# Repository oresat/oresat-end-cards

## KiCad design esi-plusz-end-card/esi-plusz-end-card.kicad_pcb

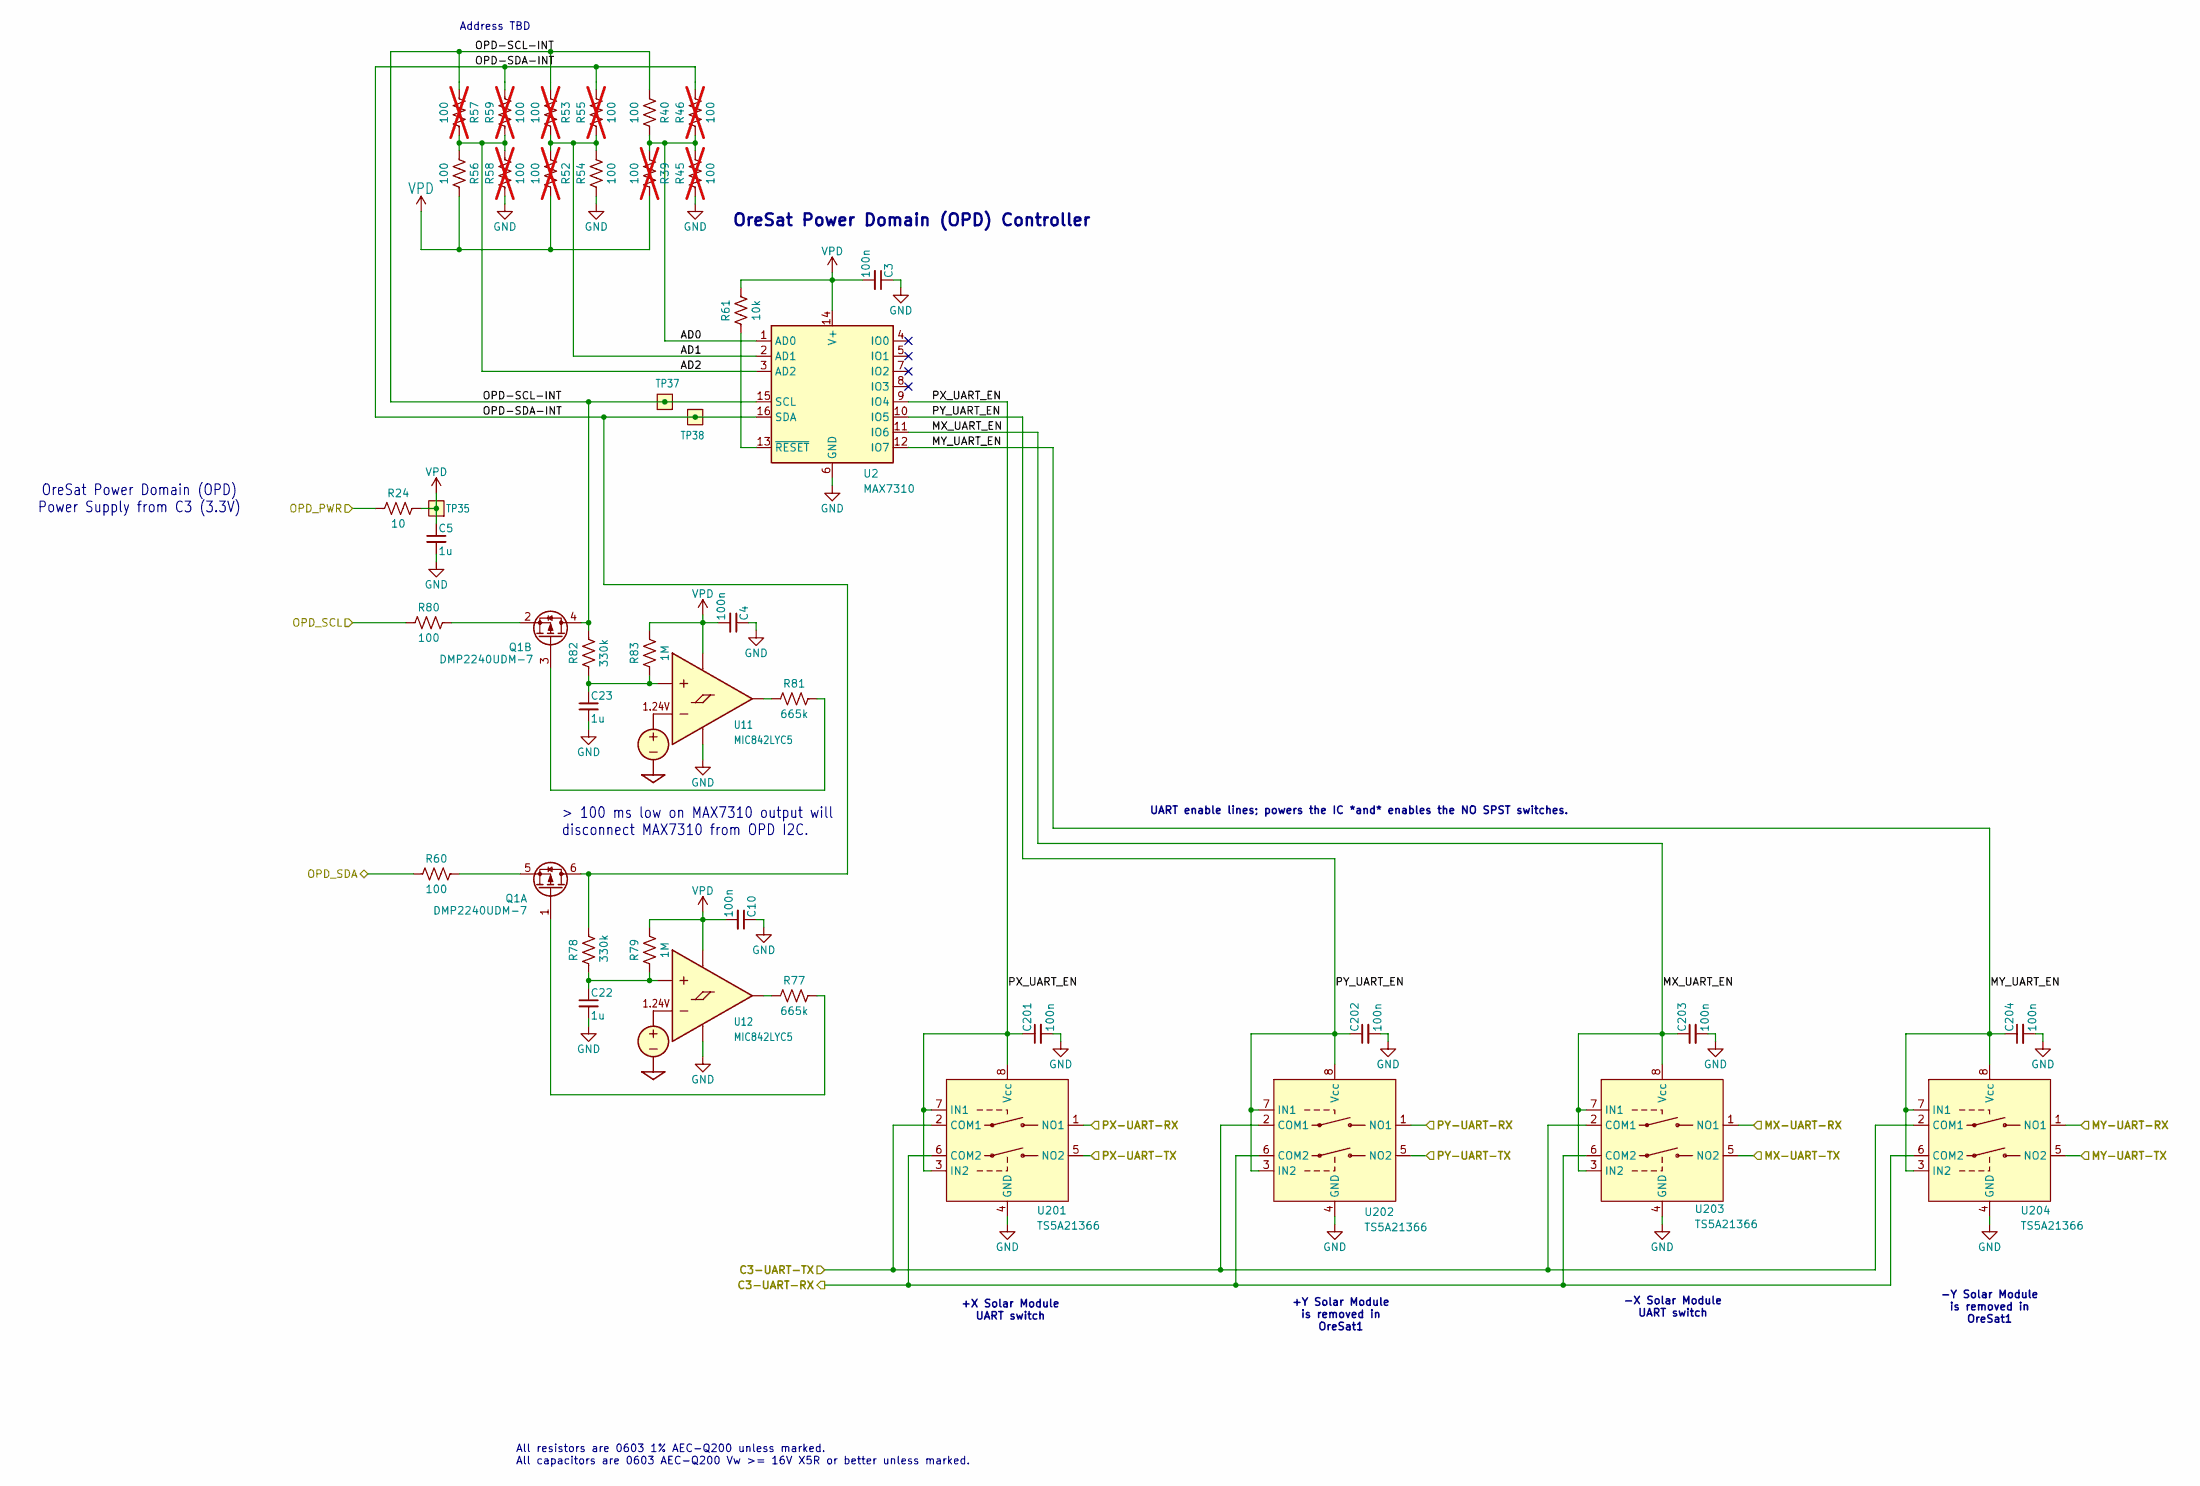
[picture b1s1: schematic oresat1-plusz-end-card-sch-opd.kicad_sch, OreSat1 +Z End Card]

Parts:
C3, C4, C10, C201, C202, C203, C204: 100n; 0603-C-NOSILK; MPN C0603C104K5RACAUTO
C5, C22, C23: 1u; 0603-C-NOSILK; MPN GRT188R71E105KE13D
Q1: DMP2240UDM-7; SOT-23-6; MPN DMP2240UDM-7
R24: 10; 0603-C-NOSILK; MPN RMCF0603FT10R0
R39, R45, R46, R52, R53, R55, R57, R58, R59: 100; 0603-C-NOSILK; MPN RMCF0603FT100R; not fitted
R40, R54, R56, R60, R80: 100; 0603-C-NOSILK; MPN RMCF0603FT100R
R61: 10k; 0603-C-NOSILK; MPN RMCF0603FT10K0
R77, R81: 665k; 0603-C-NOSILK; MPN RMCF0603FT665K
R78, R82: 330k; 0603-C-NOSILK; MPN RMCF0603FT330K
R79, R83: 1M; 0603-C-NOSILK; MPN RMCF0603FT1M00
TP35, TP37, TP38: Test-Point; TestPoint-0.75mm-th
U2: MAX7310; QFN-16-1EP_4x4mm_P0.65mm_EP2.1x2.1mm; MPN MAX7310ATE+
U11, U12: MIC842LYC5; SOT-353_SC-70-5; MPN MIC842LYC5-TR
U201, U202, U203, U204: TS5A21366; VSSOP-8_2.3x2mm_P0.5mm; MPN TS5A21366DCUR

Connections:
/+Z EC OreSat Power Domain (OPD)/AD0: R39.1, R40.2, R45.2, R46.1, U2.1 (AD0)
/+Z EC OreSat Power Domain (OPD)/AD1: R52.1, R53.2, R54.2, R55.1, U2.2 (AD1)
/+Z EC OreSat Power Domain (OPD)/AD2: R56.1, R57.2, R58.2, R59.1, U2.3 (AD2)
/+Z EC OreSat Power Domain (OPD)/MX-UART-RX: U203.1 (NO1); also elsewhere on the board
/+Z EC OreSat Power Domain (OPD)/MX-UART-TX: U203.5 (NO2); also elsewhere on the board
/+Z EC OreSat Power Domain (OPD)/MX_UART_EN: C203.1, U2.11 (IO6), U203.3 (IN2), U203.7 (IN1), U203.8 (Vcc)
/+Z EC OreSat Power Domain (OPD)/MY-UART-RX: U204.1 (NO1); also elsewhere on the board
/+Z EC OreSat Power Domain (OPD)/MY-UART-TX: U204.5 (NO2); also elsewhere on the board
/+Z EC OreSat Power Domain (OPD)/MY_UART_EN: C204.1, U2.12 (IO7), U204.3 (IN2), U204.7 (IN1), U204.8 (Vcc)
/+Z EC OreSat Power Domain (OPD)/OPD-SCL-INT: Q1.4 (D), R40.1, R53.1, R57.1, R82.2, TP37.1 (1_1), U2.15 (SCL)
/+Z EC OreSat Power Domain (OPD)/OPD-SDA-INT: Q1.6 (D), R46.2, R55.2, R59.2, R78.2, TP38.1 (1_1), U2.16 (SDA)
/+Z EC OreSat Power Domain (OPD)/PX-UART-RX: U201.1 (NO1); also elsewhere on the board
/+Z EC OreSat Power Domain (OPD)/PX-UART-TX: U201.5 (NO2); also elsewhere on the board
/+Z EC OreSat Power Domain (OPD)/PX_UART_EN: C201.1, U2.9 (IO4), U201.3 (IN2), U201.7 (IN1), U201.8 (Vcc)
/+Z EC OreSat Power Domain (OPD)/PY-UART-RX: U202.1 (NO1); also elsewhere on the board
/+Z EC OreSat Power Domain (OPD)/PY-UART-TX: U202.5 (NO2); also elsewhere on the board
/+Z EC OreSat Power Domain (OPD)/PY_UART_EN: C202.1, U2.10 (IO5), U202.3 (IN2), U202.7 (IN1), U202.8 (Vcc)
/C3_UART_RX: U201.6 (COM2), U202.6 (COM2), U203.6 (COM2), U204.6 (COM2); also elsewhere on the board
/C3_UART_TX: U201.2 (COM1), U202.2 (COM1), U203.2 (COM1), U204.2 (COM1); also elsewhere on the board
/OPD_PWR: R24.1; also elsewhere on the board
/OPD_SCL: R80.1; also elsewhere on the board
/OPD_SDA: R60.1; also elsewhere on the board
GND: C3.1, C4.1, C5.2, C10.1, C22.2, C23.2, C201.2, C202.2, C203.2, C204.2, R45.1, R54.1, R58.1, U2.6 (GND), U2.17 (GND), U11.2 (GND), U12.2 (GND), U201.4 (GND), U202.4 (GND), U203.4 (GND), U204.4 (GND); also elsewhere on the board
unnamed: Q1.1 (G), R77.2
unnamed: Q1.5 (S), R60.2
unnamed: Q1.3 (G), R81.2
unnamed: Q1.2 (S), R80.2
unnamed: R61.1, U2.13 (~RESET)
unnamed: C23.1, R82.1, R83.1, U11.1 (INP)
unnamed: R81.1, U11.4 (OUT)
unnamed: C22.1, R78.1, R79.1, U12.1 (INP)
unnamed: R77.1, U12.4 (OUT)
VPD: C3.2, C4.2, C5.1, C10.2, R24.2, R39.2, R52.2, R56.2, R61.2, R79.2, R83.2, TP35.1 (1_1), U2.14 (V+), U11.5 (VDD), U12.5 (VDD)

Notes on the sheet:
-X Solar Module UART switch
OreSat Power Domain (OPD) Power Supply from C3 (3.3V)
All resistors are 0603 1% AEC-Q200 unless marked. All capacitors are 0603 AEC-Q200 Vw >= 16V X5R or better unless marked.
+Y Solar Module is removed in OreSat1
OreSat Power Domain (OPD) Controller
-Y Solar Module is removed in OreSat1
> 100 ms low on MAX7310 output will disconnect MAX7310 from OPD I2C.
Address TBD
UART enable lines; powers the IC *and* enables the NO SPST switches.
+X Solar Module UART switch

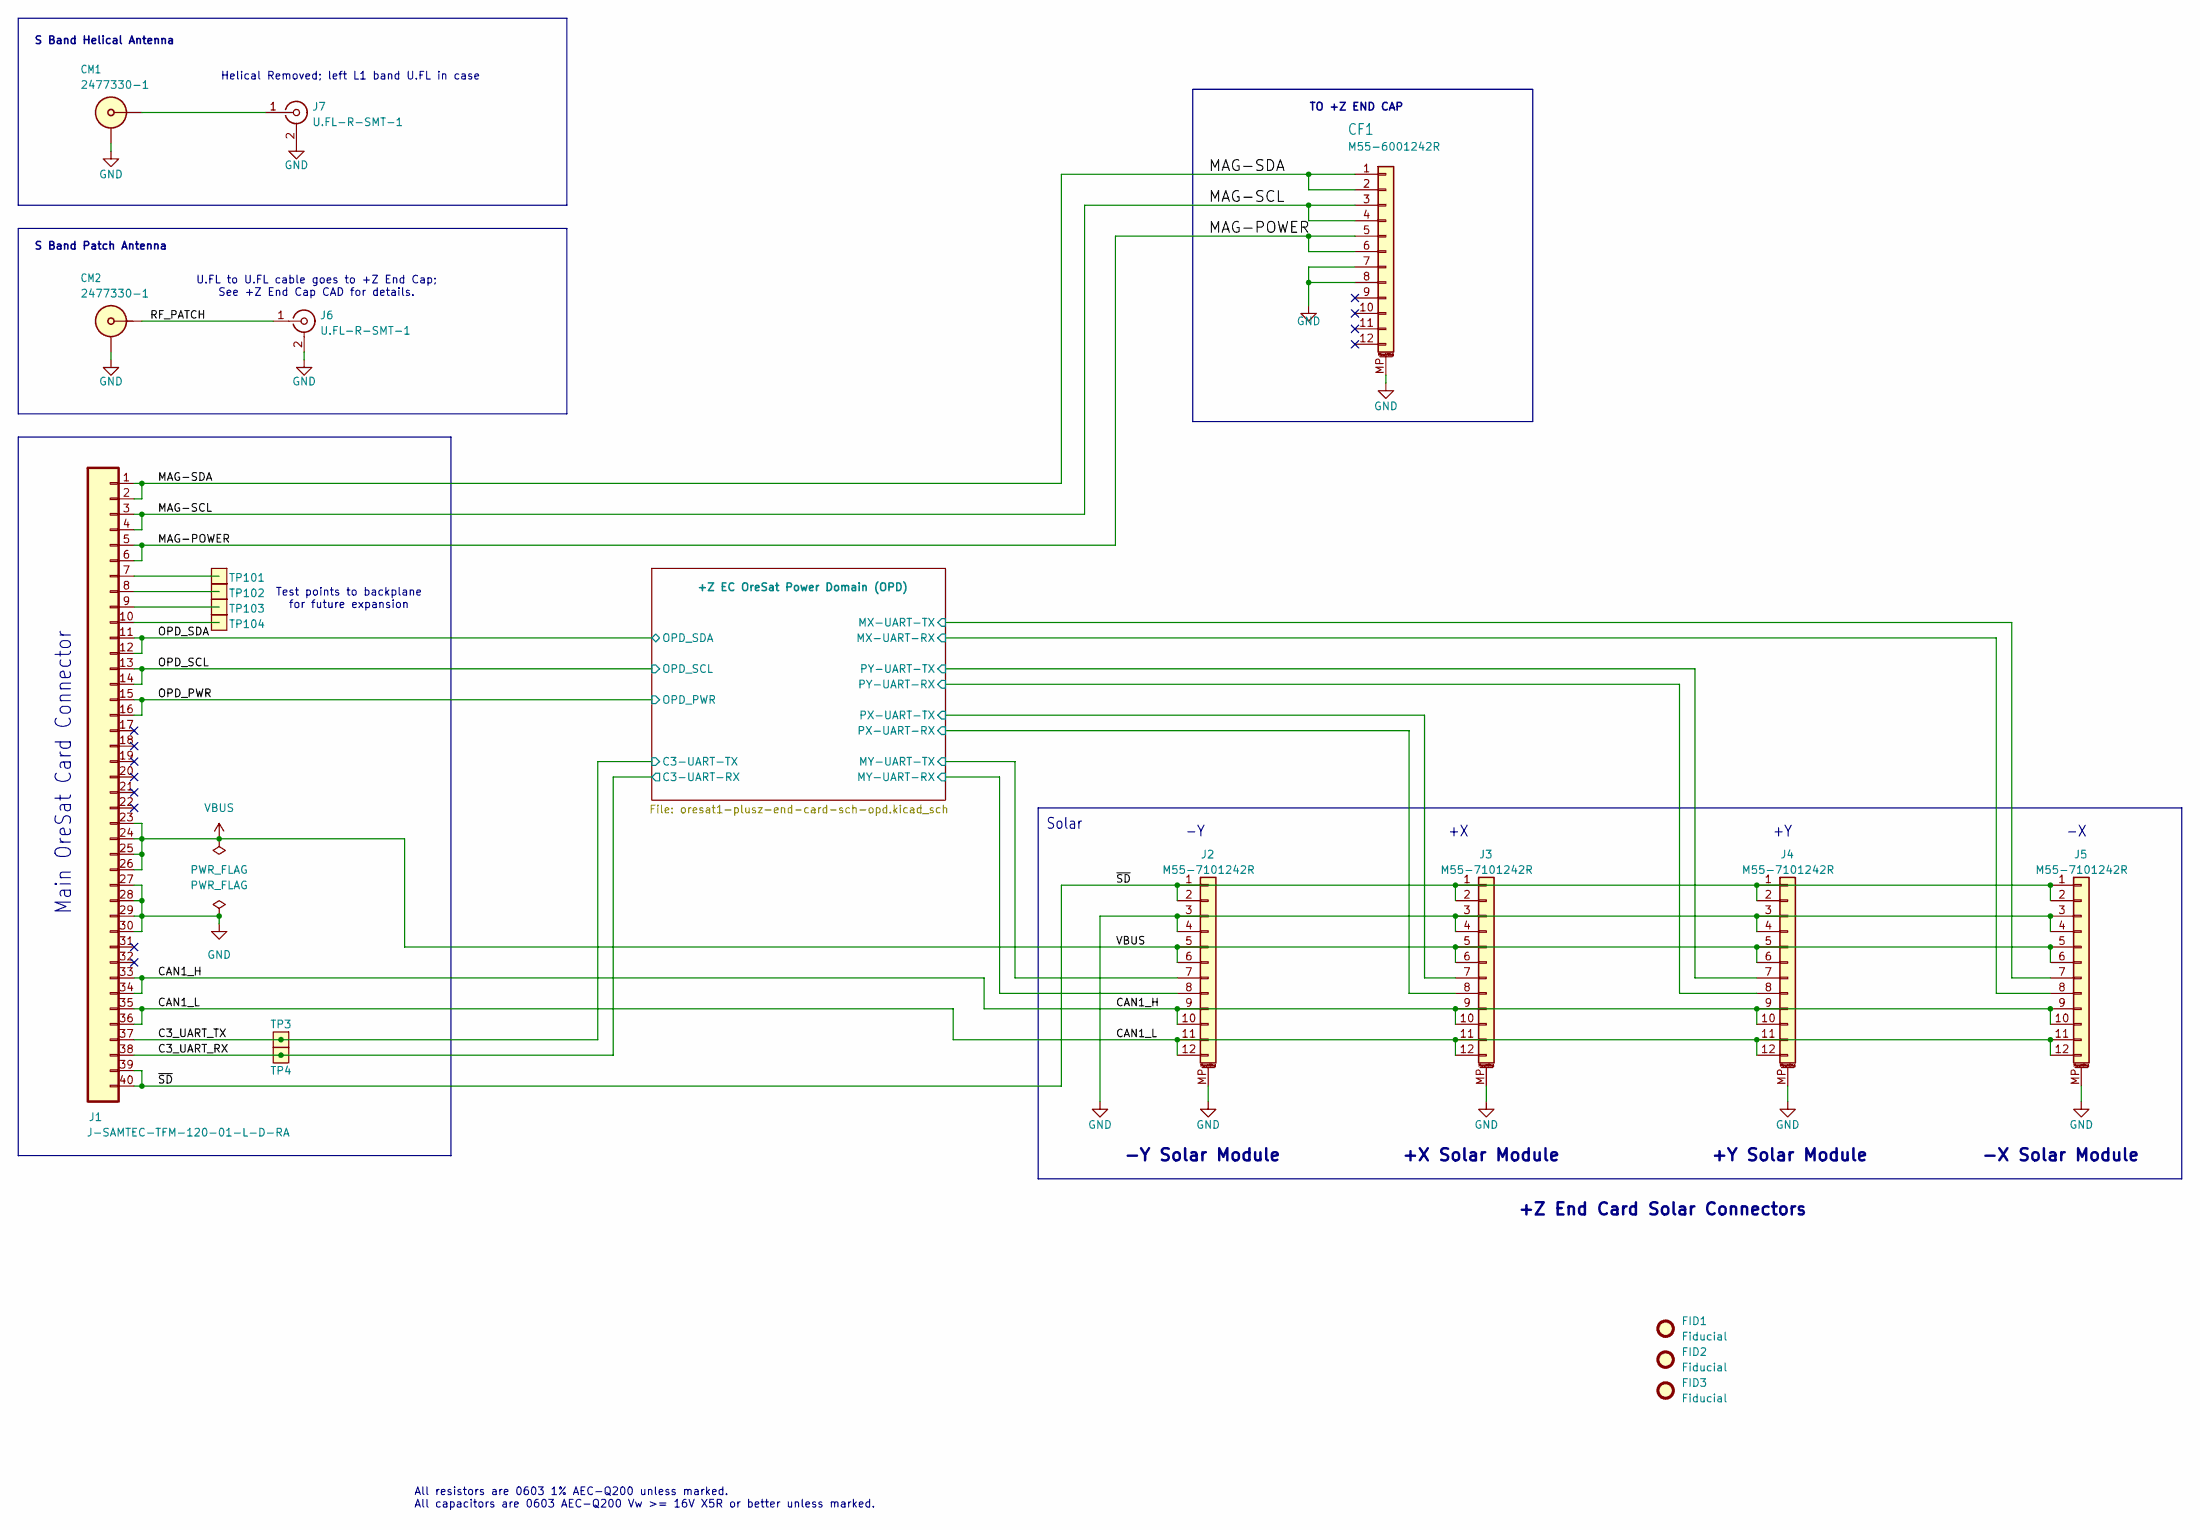
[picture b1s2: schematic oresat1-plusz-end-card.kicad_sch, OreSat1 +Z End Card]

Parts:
CF1: M55-6001242R; J-Harwin-M55-60X1242R; MPN M55-6001242R
CM1, CM2: 2477330-1; J-MOLEX-SMPM-073300-002X; MPN 2477330-1
FID1, FID2, FID3: Fiducial; Fiducial_1mm_Mask2mm
J1: J-SAMTEC-TFM-120-01-L-D-RA; J-SAMTEC-TFM-120-X1-XXX-D-RA; MPN TFM-120-01-L-D-RA
J2, J3, J4, J5: M55-7101242R; J-Harwin-M55-7101242R; MPN M55-7101242R
J6, J7: U.FL-R-SMT-1; U.FL_Hirose_U.FL-R-SMT-1_Vertical; MPN U.FL-R-SMT-1(10)
TP3, TP4, TP101, TP102, TP103, TP104: TestPoint-MinTH; TestPoint-0.75mm-th

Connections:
/+Z EC OreSat Power Domain (OPD)/MX-UART-RX: J5.8; also elsewhere on the board
/+Z EC OreSat Power Domain (OPD)/MX-UART-TX: J5.7; also elsewhere on the board
/+Z EC OreSat Power Domain (OPD)/MY-UART-RX: J2.8; also elsewhere on the board
/+Z EC OreSat Power Domain (OPD)/MY-UART-TX: J2.7; also elsewhere on the board
/+Z EC OreSat Power Domain (OPD)/PX-UART-RX: J3.8; also elsewhere on the board
/+Z EC OreSat Power Domain (OPD)/PX-UART-TX: J3.7; also elsewhere on the board
/+Z EC OreSat Power Domain (OPD)/PY-UART-RX: J4.8; also elsewhere on the board
/+Z EC OreSat Power Domain (OPD)/PY-UART-TX: J4.7; also elsewhere on the board
/C3_UART_RX: J1.38, TP4.1 (1_1); also elsewhere on the board
/C3_UART_TX: J1.37, TP3.1 (1_1); also elsewhere on the board
/CAN1_H: J1.33, J1.34, J2.9, J2.10, J3.9, J3.10, J4.9, J4.10, J5.9, J5.10
/CAN1_L: J1.35, J1.36, J2.11, J2.12, J3.11, J3.12, J4.11, J4.12, J5.11, J5.12
/MAG-POWER: CF1.5, CF1.6, J1.5, J1.6
/MAG-SCL: CF1.3, CF1.4, J1.3, J1.4
/MAG-SDA: CF1.1, CF1.2, J1.1, J1.2
/OPD_PWR: J1.15, J1.16; also elsewhere on the board
/OPD_SCL: J1.13, J1.14; also elsewhere on the board
/OPD_SDA: J1.11, J1.12; also elsewhere on the board
/RF_L1: CM1.SIG, J7.1 (In)
/RF_PATCH: CM2.SIG, J6.1 (In)
/~SD: J1.39, J1.40, J2.1, J2.2, J3.1, J3.2, J4.1, J4.2, J5.1, J5.2
GND: CF1.7, CF1.8, CF1.MP (MountPin), CM1.SHLD, CM2.SHLD, J1.27, J1.28, J1.29, J1.30, J2.3, J2.4, J2.MP (MountPin), J3.3, J3.4, J3.MP (MountPin), J4.3, J4.4, J4.MP (MountPin), J5.3, J5.4, J5.MP (MountPin), J6.2 (Ext), J7.2 (Ext); also elsewhere on the board
unnamed: J1.7, TP101.1 (1_1)
unnamed: J1.8, TP102.1 (1_1)
unnamed: J1.9, TP103.1 (1_1)
unnamed: J1.10, TP104.1 (1_1)
VBUS: J1.23, J1.24, J1.25, J1.26, J2.5, J2.6, J3.5, J3.6, J4.5, J4.6, J5.5, J5.6

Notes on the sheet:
TO +Z END CAP
U.FL to U.FL cable goes to +Z End Cap; See +Z End Cap CAD for details.
Test points to backplane for future expansion
+Z End Card Solar Connectors
-X Solar Module
S Band Helical Antenna
Solar
+X Solar Module
S Band Patch Antenna
+Y Solar Module
All resistors are 0603 1% AEC-Q200 unless marked. All capacitors are 0603 AEC-Q200 Vw >= 16V X5R or better unless marked.
Helical Removed; left L1 band U.FL in case
Main OreSat Card Connector
-Y Solar Module

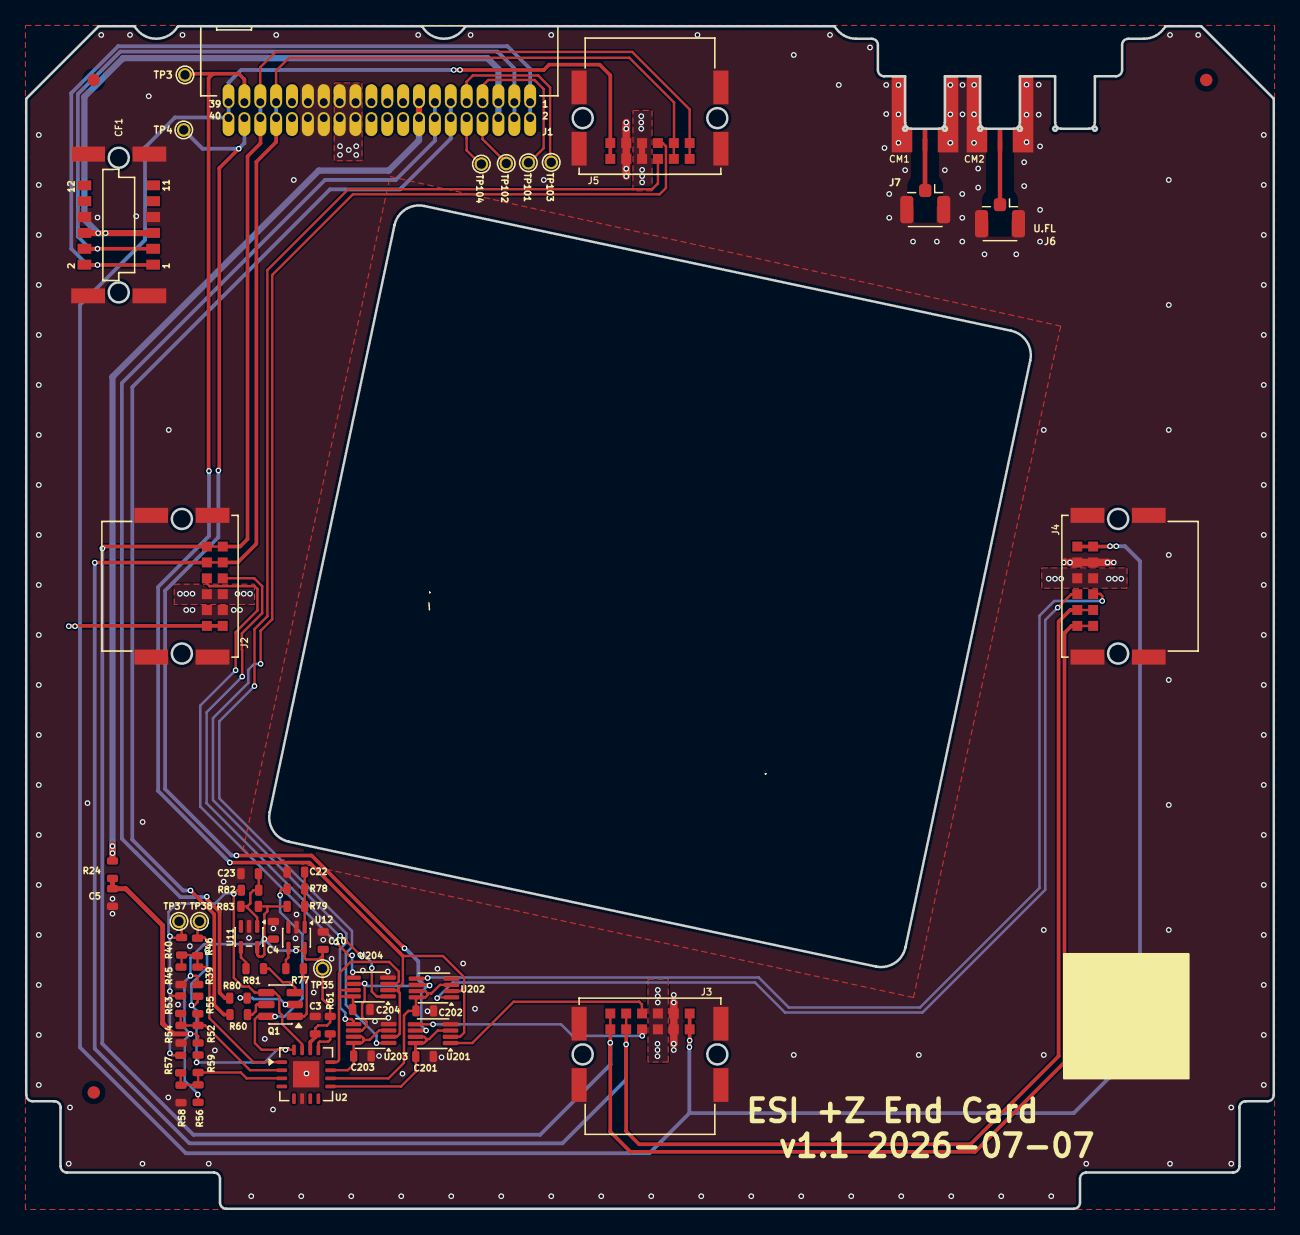
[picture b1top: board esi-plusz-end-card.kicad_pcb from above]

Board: 4 copper layers, 99.8 x 94.6 mm, 62 parts (0 on the bottom side), 46 nets.

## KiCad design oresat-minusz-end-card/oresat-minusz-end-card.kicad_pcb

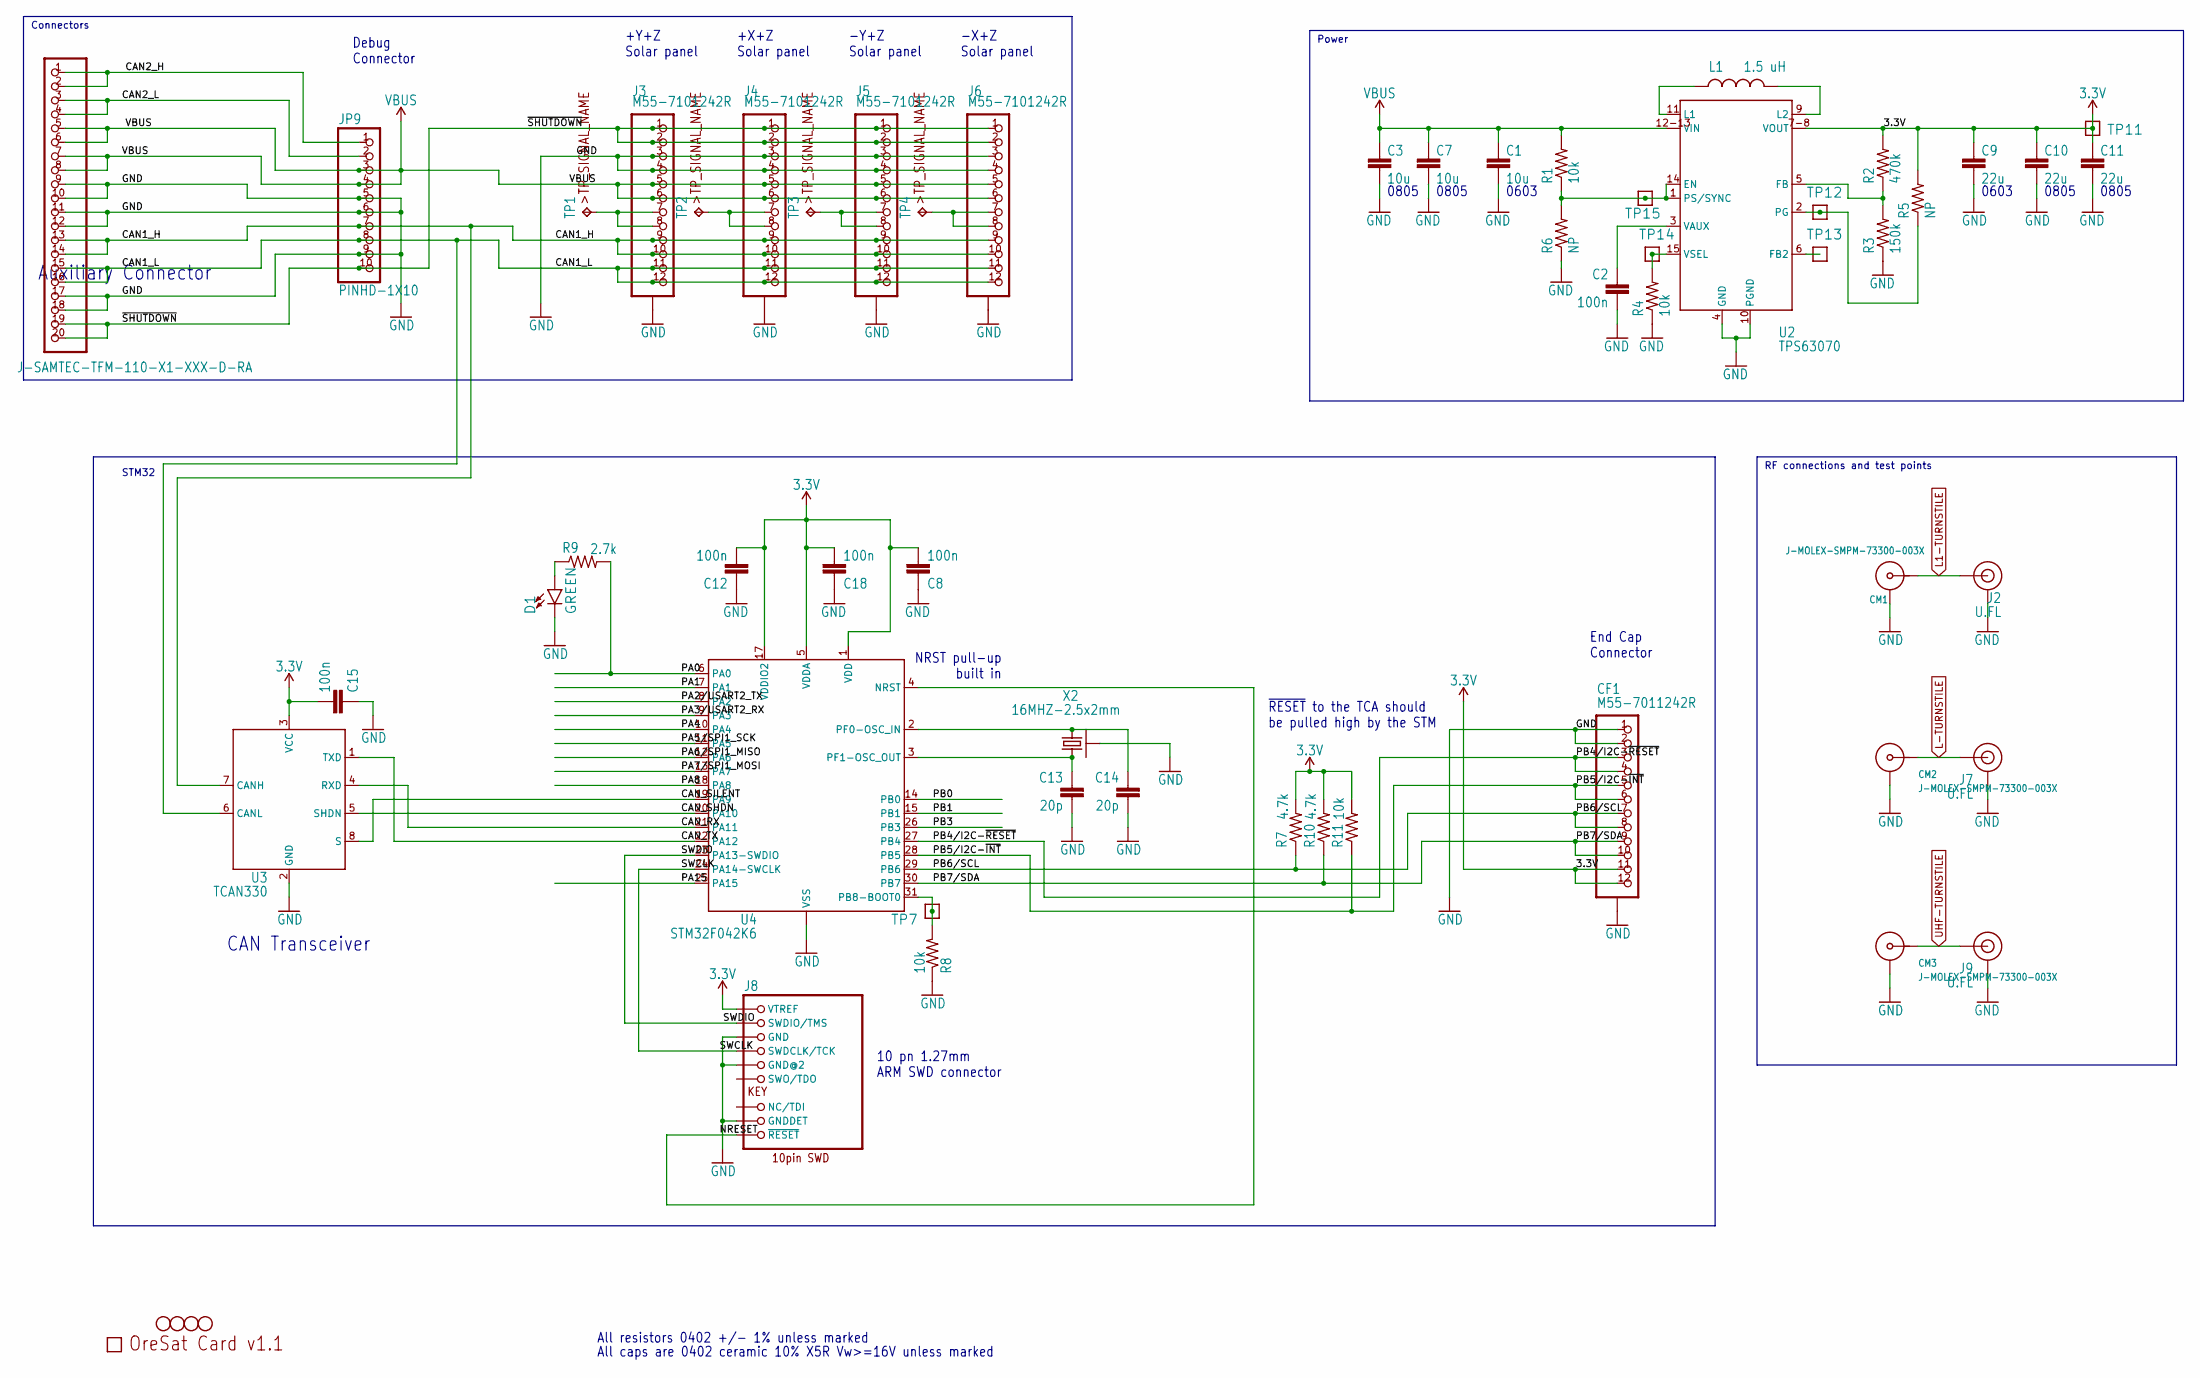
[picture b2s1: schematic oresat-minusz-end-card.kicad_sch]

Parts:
C1, C9: .0603-B-NOSILK
C2, C8, C12, C13, C14, C15, C18: .0402-B-NOSILK
C3, C7: 10u; .0805-B-NOSILK
C10, C11: 22u; .0805-B-NOSILK
CARD0: ORESAT-CARD-V0.5; ORESAT-CARD-V1.0
CF1: M55-7011242R; HARWIN-M55-6021242R
CM1, CM2, CM3: J-MOLEX-SMPM-73300-003X; J-MOLEX-SMPM-073300-003X
D1: GREEN; LED-0603
H1, H2, H3, H4: STAND-OFFTIGHT; STAND-OFF-TIGHT
J1: J-SAMTEC-TFM-110-X1-XXX-D-RA
J2, J7, J9: U.FL; J-U.FL
J3, J4, J5, J6: M55-7101242R
J8: CON10_2X5_DUK_FTSH
JP9: PINHD-1X10; 1X10
L1: L-COILCRAFT-XFL4020
R1, R2, R3, R4, R5, R6, R7, R8, R9, R10, R11: .0402-B-NOSILK
TP1, TP2, TP3, TP4: TPPAD1-13; P1-13
TP7, TP11, TP12, TP13, TP14, TP15: TEST-POINT; 2MM-TEST-POINT
U2: TPS63070X
U3: SOT23-8_TI-DCN
U4: QFP32-7X7
X2: CRYSTAL_2.5X2

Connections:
3.3V: C8.2, C9.1, C10.1, C11.1, C12.2, C15.2, C18.2, CF1.11, CF1.12, J8.1 (VTREF), R2.2, R5.2, R7.2, R10.2, R11.2, TP11.1, U2.7-8 (VOUT), U3.3 (VCC), U4.1 (VDD), U4.5 (VDDA), U4.17 (VDDIO2)
/CAN1_H: J1.13, J1.14, J3.9, J3.10, J4.9, J4.10, J5.9, J5.10, J6.9, J6.10, JP9.7, U3.7 (CANH)
/CAN1_L: J1.15, J1.16, J3.11, J3.12, J4.11, J4.12, J5.11, J5.12, J6.11, J6.12, JP9.8, U3.6 (CANL)
/CAN2_H: J1.1, J1.2, JP9.1
/CAN2_L: J1.3, J1.4, JP9.2
/CAN_RX: U3.4 (RXD), U4.21 (PA11)
/CAN_SHDN: U3.5 (SHDN), U4.20 (PA10)
/CAN_SILENT: U3.8 (S), U4.19 (PA9)
/CAN_TX: U3.1 (TXD), U4.22 (PA12)
/NRESET: J8.10 (~RESET), U4.4 (NRST)
/PA0: R9.2, U4.6 (PA0)
/PA1: U4.7 (PA1)
/PA2/USART2_TX: U4.8 (PA2)
/PA3/USART2_RX: U4.9 (PA3)
/PA4: U4.10 (PA4)
/PA5/SPI1_SCK: U4.11 (PA5)
/PA6/SPI1_MISO: U4.12 (PA6)
/PA7/SPI1_MOSI: U4.13 (PA7)
/PA8: U4.18 (PA8)
/PA15: U4.25 (PA15)
/PB0: U4.14 (PB0)
/PB1: U4.15 (PB1)
/PB3: U4.26 (PB3)
/PB4/I2C-~RESET: CF1.3, CF1.4, U4.27 (PB4)
/PB5/I2C-~INT: CF1.5, CF1.6, R11.1, U4.28 (PB5)
/PB6/SCL: CF1.7, CF1.8, R7.1, U4.29 (PB6)
/PB7/SDA: CF1.9, CF1.10, R10.1, U4.30 (PB7)
/SWCLK: J8.4 (SWDCLK/TCK), U4.24 (PA14-SWCLK)
/SWDIO: J8.2 (SWDIO/TMS), U4.23 (PA13-SWDIO)
/~SHUTDOWN: J1.19, J1.20, J3.1, J3.2, J4.1, J4.2, J5.1, J5.2, J6.1, J6.2, JP9.10
GND: C1.2, C2.2, C3.2, C7.2, C8.1, C9.2, C10.2, C11.2, C12.1, C13.2, C14.2, C15.1, C18.1, CF1.1, CF1.2, CF1.P$1 (SHIELDS), CF1.P$2 (SHIELDS), CF1.P$3 (SHIELDS), CF1.P$4 (SHIELDS), CM1.GND (SHIELD3), CM2.GND (SHIELD3), CM3.GND (SHIELD3), D1.C, J1.9, J1.10, J1.11, J1.12, J1.17, J1.18, J2.GND, J3.3, J3.4, J3.P$1 (SHIELD), J3.P$2 (SHIELD), J3.P$3 (SHIELD), J3.P$4 (SHIELD), J4.3, J4.4, J4.P$1 (SHIELD), J4.P$2 (SHIELD), J4.P$3 (SHIELD), J4.P$4 (SHIELD), J5.3, J5.4, J5.P$1 (SHIELD), J5.P$2 (SHIELD), J5.P$3 (SHIELD), J5.P$4 (SHIELD), J6.3, J6.4, J6.P$1 (SHIELD), J6.P$2 (SHIELD), J6.P$3 (SHIELD), J6.P$4 (SHIELD), J7.GND, J8.3 (GND), J8.5 (GND@2), J8.9 (GNDDET), J9.GND, JP9.5, JP9.6, JP9.9, R3.1, R4.1, R6.1, R8.1, U2.4 (GND), U2.10 (PGND), U3.2 (GND), U4.16 (VSS), U4.32 (VSS), X2.2 (SHIELD), X2.4 (SHIELD)
L1-TURNSTILE: CM1.RF (CENTER), J2.FEED (SIGNAL)
L-TURNSTILE: CM2.RF (CENTER), J7.FEED (SIGNAL)
unnamed: C2.1, U2.3 (VAUX)
unnamed: C13.1, U4.3 (PF1-OSC_OUT), X2.3 (2)
unnamed: C14.1, U4.2 (PF0-OSC_IN), X2.1
unnamed: D1.A, R9.1
unnamed: J3.7, J3.8, TP1.TP
unnamed: J4.7, J4.8, TP2.TP
unnamed: J5.7, J5.8, TP3.TP
unnamed: J6.7, J6.8, TP4.TP
unnamed: L1.1, U2.11 (L1)
unnamed: L1.2, U2.9 (L2)
unnamed: R1.1, R6.2, TP15.1, U2.1 (PS/SYNC), U2.14 (EN)
unnamed: R2.1, R3.2, U2.5 (FB)
unnamed: R4.2, TP14.1, U2.15 (VSEL)
unnamed: R5.1, TP12.1, U2.2 (PG)
unnamed: R8.2, TP7.1, U4.31 (PB8-BOOT0)
unnamed: TP13.1, U2.6 (FB2)
UHF-TURNSTILE: CM3.RF (CENTER), J9.FEED (SIGNAL)
VBUS: C1.1, C3.1, C7.1, J1.5, J1.6, J1.7, J1.8, J3.5, J3.6, J4.5, J4.6, J5.5, J5.6, J6.5, J6.6, JP9.3, JP9.4, R1.2, U2.12-13 (VIN)

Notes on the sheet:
RF connections and test points
0805
10 pn 1.27mm ARM SWD connector
0603
CAN Transceiver
+Y+Z Solar panel
All resistors 0402 +/- 1% unless marked
Power
+X+Z Solar panel
-Y+Z Solar panel
All caps are 0402 ceramic 10% X5R Vw>=16V unless marked
Auxiliary Connector
Connectors
Debug Connector
-X+Z Solar panel
NRST pull-up built in
~{RESET} to the TCA should be pulled high by the STM
End Cap Connector
STM32

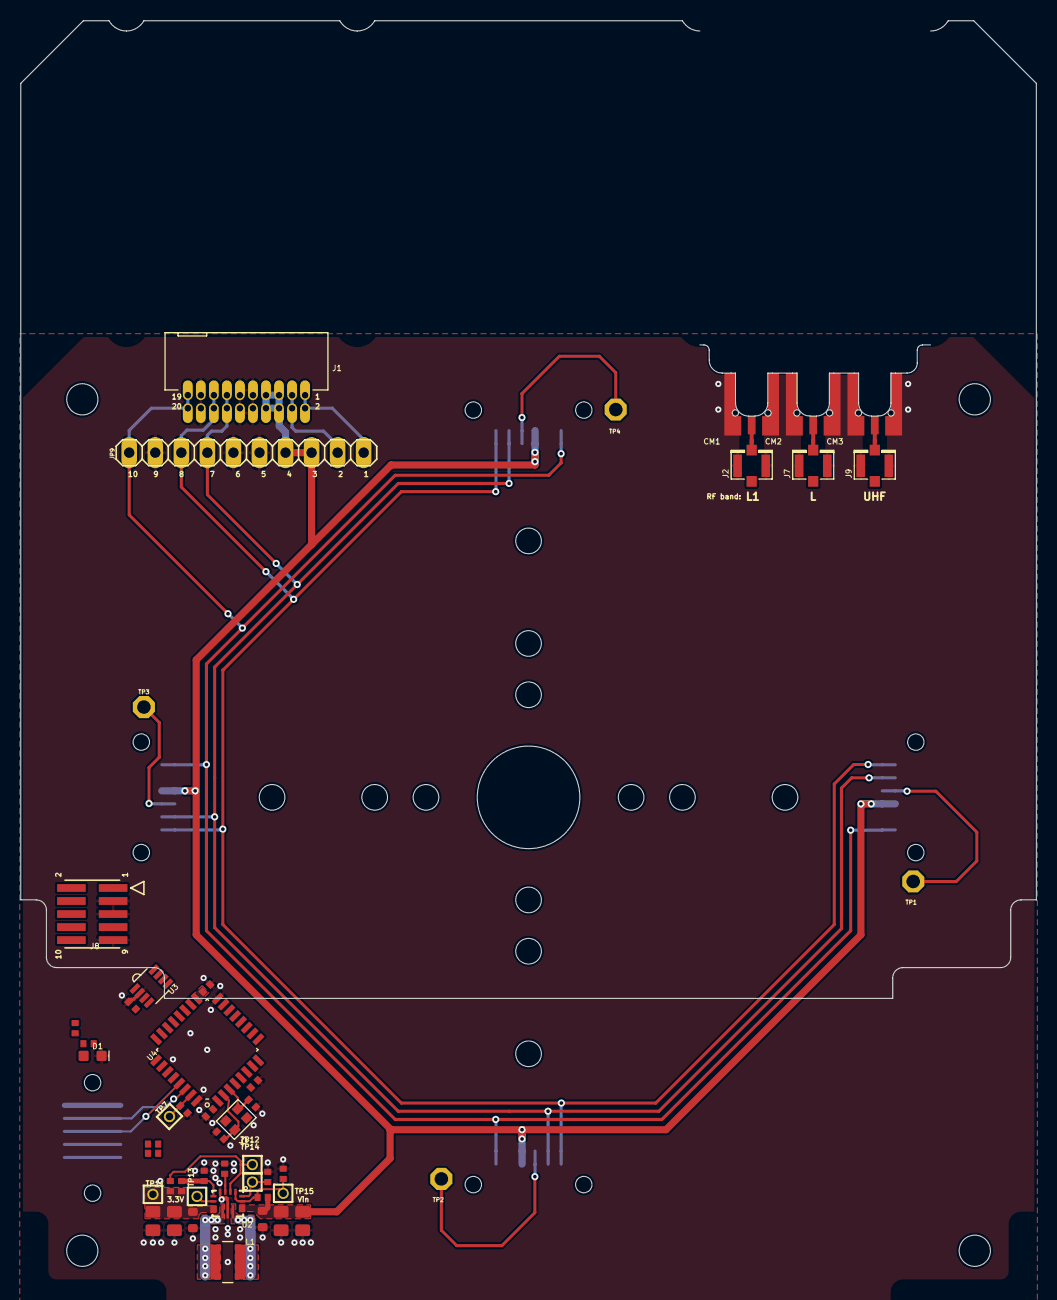
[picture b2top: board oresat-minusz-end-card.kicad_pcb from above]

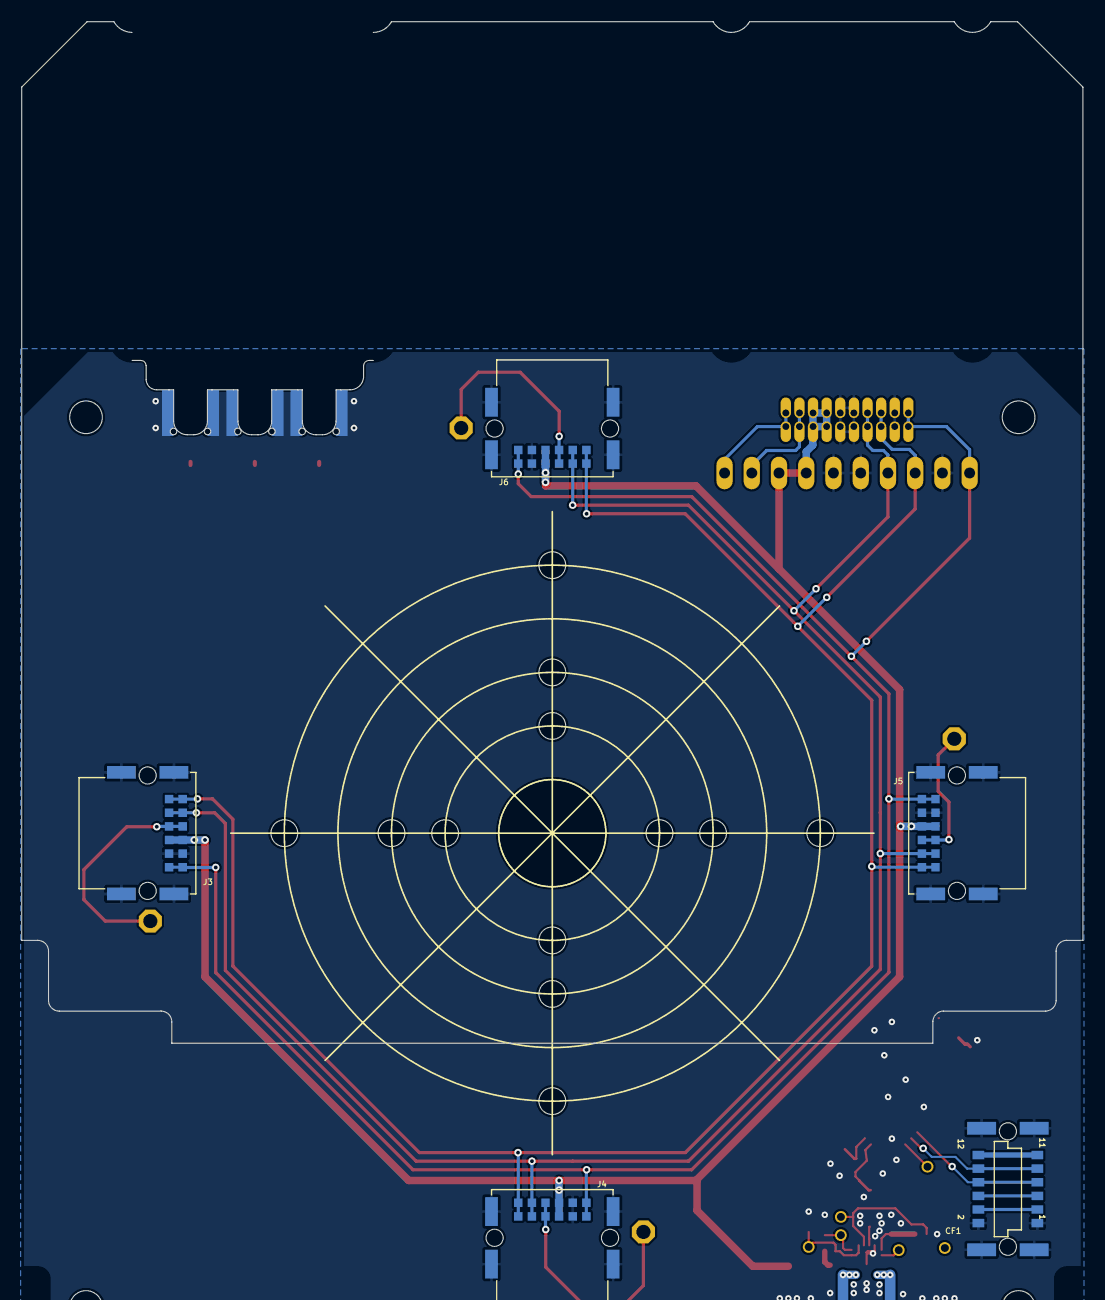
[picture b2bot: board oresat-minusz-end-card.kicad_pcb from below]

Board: 2 copper layers, 72 parts (5 on the bottom side), 39 nets.

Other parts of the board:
@HOLE0, @HOLE1, @HOLE2, @HOLE3, @HOLE4, @HOLE5, @HOLE6, @HOLE7, @HOLE8, @HOLE9, @HOLE10, @HOLE11, @HOLE12: (no value)
